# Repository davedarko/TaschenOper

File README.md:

# TaschenOper

A handheld inspired by adafruits numpad and certain pocket music devices.

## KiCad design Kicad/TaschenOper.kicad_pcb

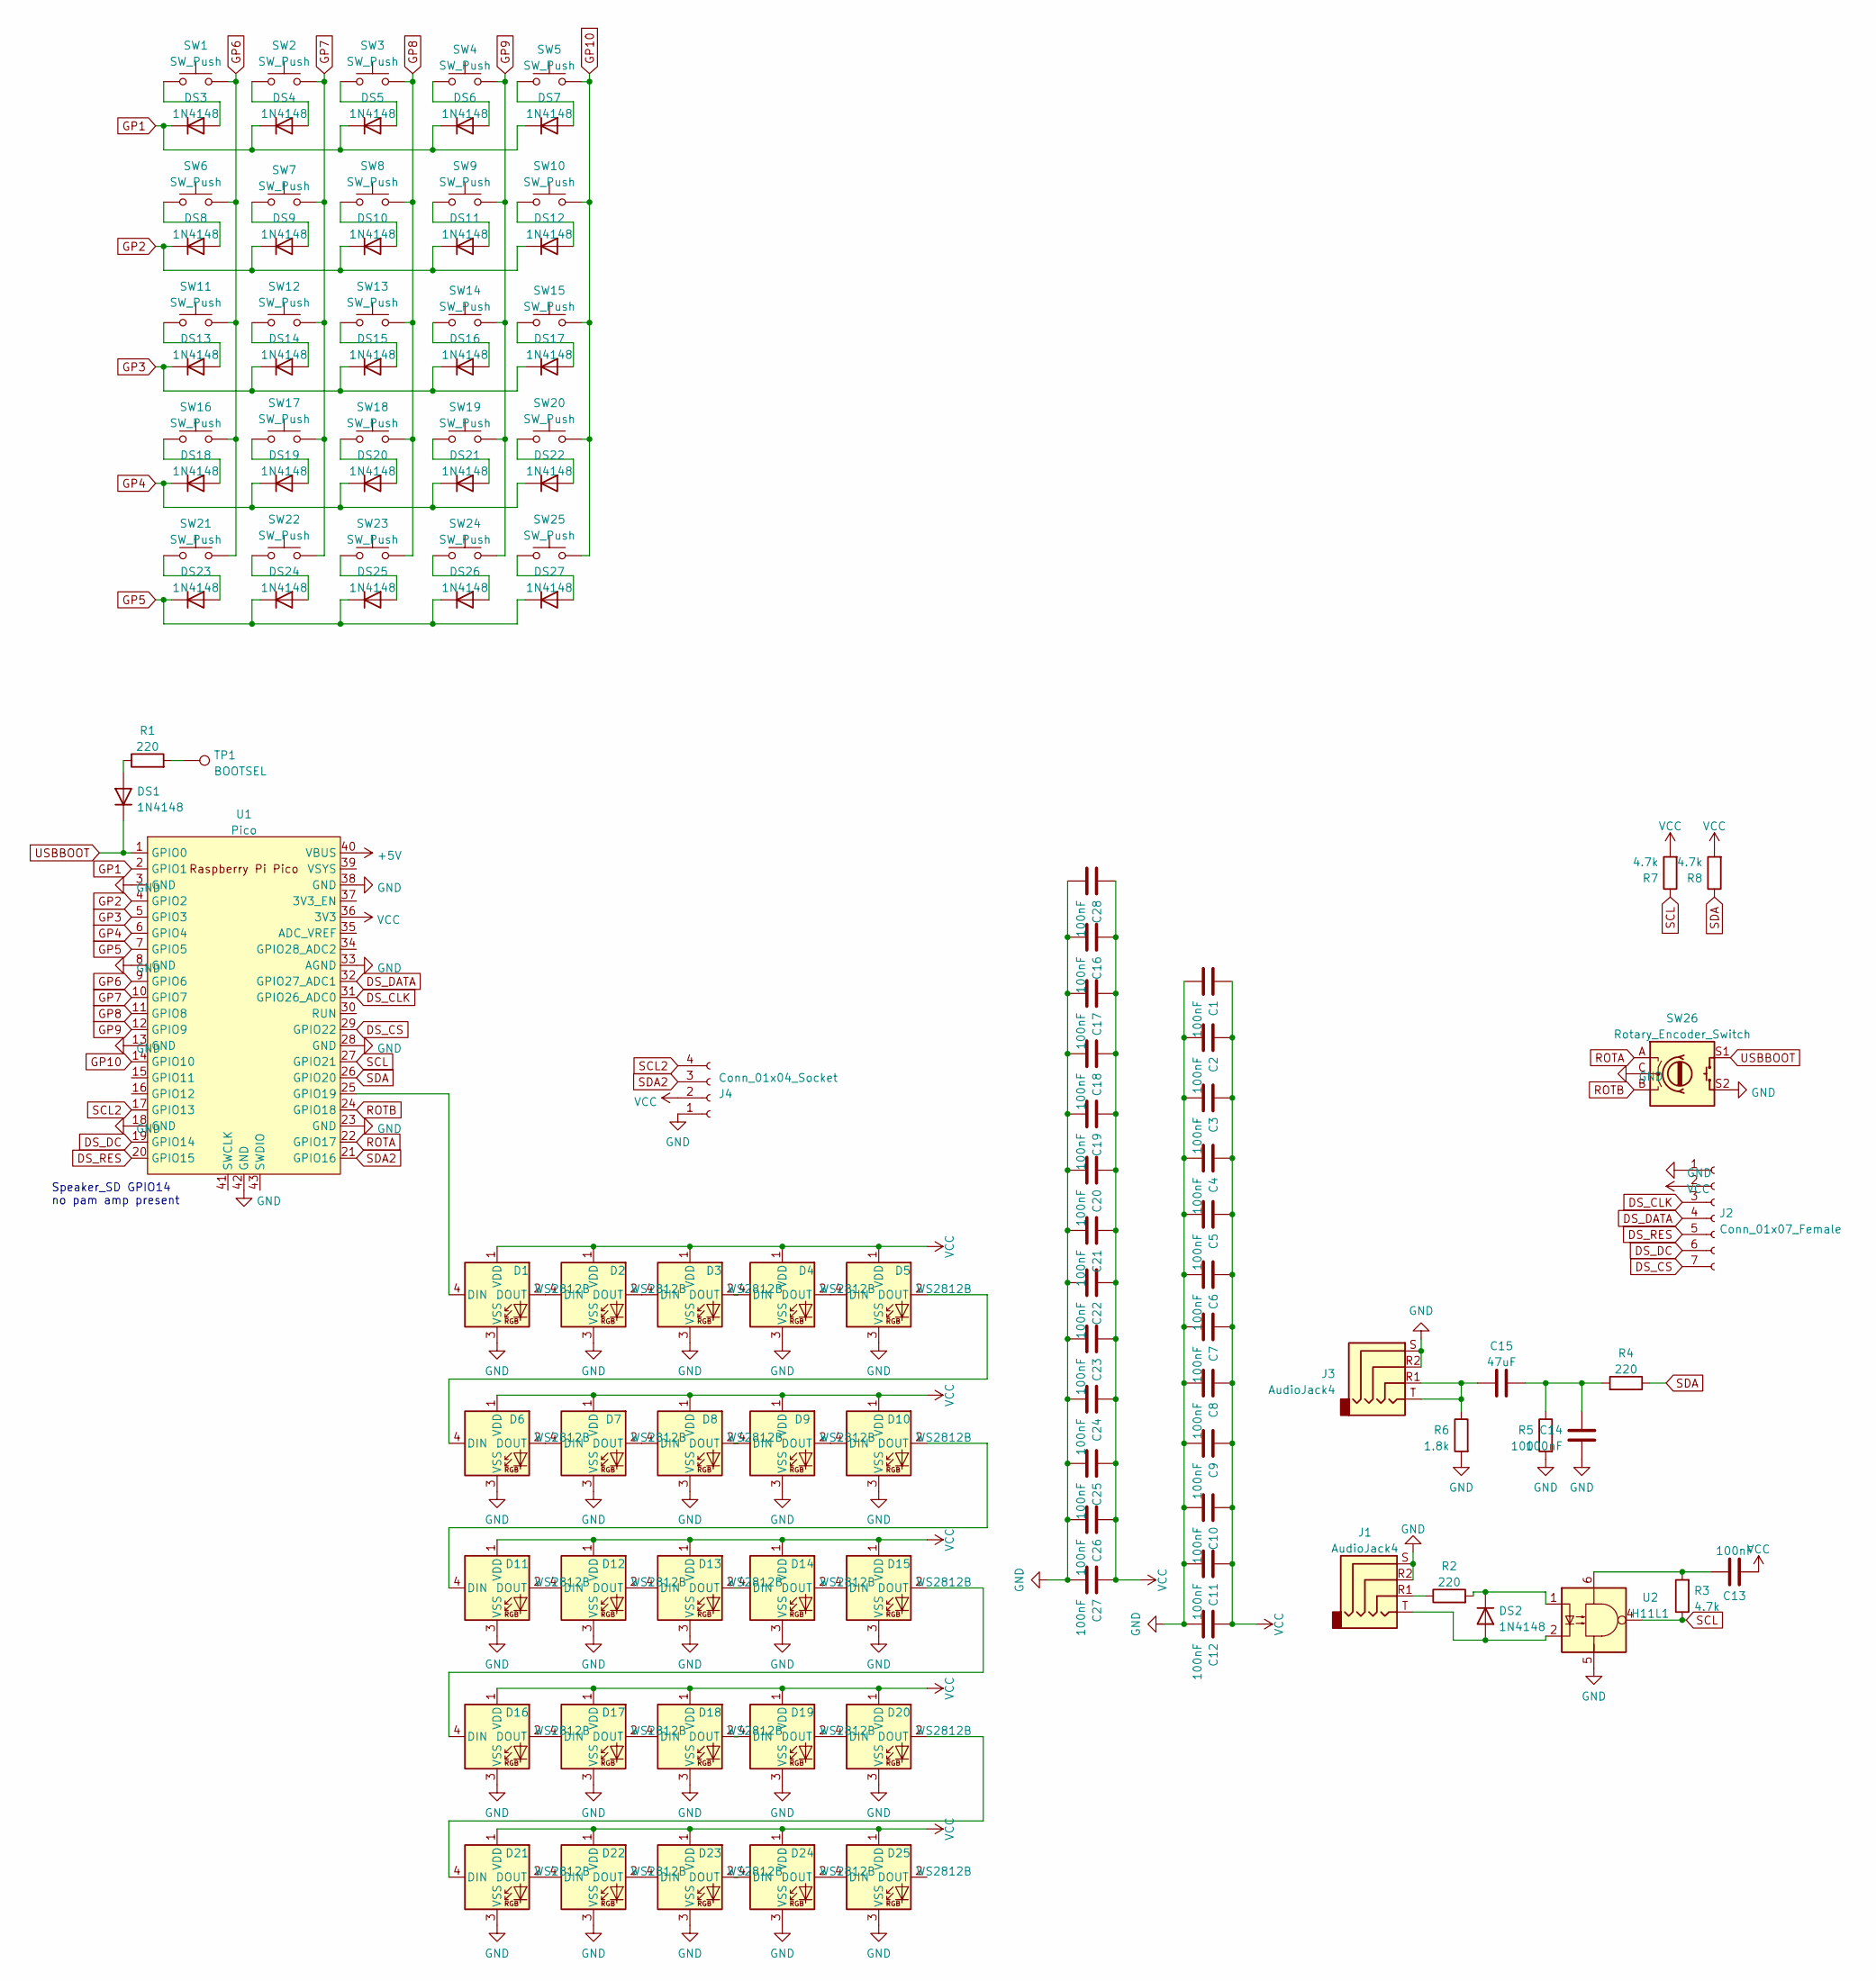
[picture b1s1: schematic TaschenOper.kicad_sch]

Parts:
C1, C2, C3, C4, C5, C6, C7, C8, C9, C10, C11, C12, C13, C14, C16, C17, C18, C19, C20, C21, C22, C23, C24, C25, C26, C27, C28: 100nF; C_0603_1608Metric_Pad1.08x0.95mm_HandSolder
C15: 47uF; C_0603_1608Metric_Pad1.08x0.95mm_HandSolder
D1, D2, D3, D4, D5, D6, D7, D8, D9, D10, D11, D12, D13, D14, D15, D16, D17, D18, D19, D20, D21, D22, D23, D24, D25: WS2812B; LED_SK6812MINI_PLCC4_3.5x3.5mm_P1.75mm
DS1, DS2, DS3, DS4, DS5, DS6, DS7, DS8, DS9, DS10, DS11, DS12, DS13, DS14, DS15, DS16, DS17, DS18, DS19, DS20, DS21, DS22, DS23, DS24, DS25, DS26, DS27: 1N4148; D_0805_2012Metric_Pad1.15x1.40mm_HandSolder
J1, J3: AudioJack4; Jack_3.5mm_PJ320D_Horizontal
J2: Conn_01x07_Female; PinHeader_1x07_P2.54mm_Vertical
J4: Conn_01x04_Socket; JST_SH_SM04B-SRSS-TB_1x04-1MP_P1.00mm_Horizontal
R1, R2, R4: 220; R_0603_1608Metric_Pad0.98x0.95mm_HandSolder
R3, R7, R8: 4.7k; R_0603_1608Metric_Pad0.98x0.95mm_HandSolder
R5: 100; R_0603_1608Metric_Pad0.98x0.95mm_HandSolder
R6: 1.8k; R_0603_1608Metric_Pad0.98x0.95mm_HandSolder
SW1, SW2, SW3, SW4, SW5, SW6, SW7, SW8, SW9, SW10, SW11, SW12, SW13, SW14, SW15, SW16, SW17, SW18, SW19, SW20, SW21, SW22, SW23, SW24, SW25: SW_Push; SW_SPST_PTS645
SW26: Rotary_Encoder_Switch; RotaryEncoder_Alps_EC11E-Switch_Vertical_H20mm_CircularMoun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
TP1: BOOTSEL; TestPoint_Pad_D1.5mm
U1: Pico; RPi_Pico_SMD
U2: H11L1; DIP-6_W8.89mm_SMDSocket_LongPads

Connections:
+5V: U1.40 (VBUS)
DS_CLK: J2.3, U1.31 (GPIO26_ADC0)
DS_CS: J2.7, U1.29 (GPIO22)
DS_DATA: J2.4, U1.32 (GPIO27_ADC1)
DS_DC: J2.6, U1.19 (GPIO14)
DS_RES: J2.5, U1.20 (GPIO15)
GND: C1.2, C2.2, C3.2, C4.2, C5.2, C6.2, C7.2, C8.2, C9.2, C10.2, C11.2, C12.2, C14.2, C16.2, C17.2, C18.2, C19.2, C20.2, C21.2, C22.2, C23.2, C24.2, C25.2, C26.2, C27.2, C28.2, D1.3 (VSS), D2.3 (VSS), D3.3 (VSS), D4.3 (VSS), D5.3 (VSS), D6.3 (VSS), D7.3 (VSS), D8.3 (VSS), D9.3 (VSS), D10.3 (VSS), D11.3 (VSS), D12.3 (VSS), D13.3 (VSS), D14.3 (VSS), D15.3 (VSS), D16.3 (VSS), D17.3 (VSS), D18.3 (VSS), D19.3 (VSS), D20.3 (VSS), D21.3 (VSS), D22.3 (VSS), D23.3 (VSS), D24.3 (VSS), D25.3 (VSS), J1.R2, J1.S, J2.1, J3.R2, J3.S, J4.1, R5.2, R6.2, SW26.C, SW26.S2, U1.3 (GND), U1.8 (GND), U1.13 (GND), U1.18 (GND), U1.23 (GND), U1.28 (GND), U1.33 (AGND), U1.38 (GND), U1.42 (GND), U2.5
GP1: DS3.1 (K), DS4.1 (K), DS5.1 (K), DS6.1 (K), DS7.1 (K), U1.2 (GPIO1)
GP2: DS8.1 (K), DS9.1 (K), DS10.1 (K), DS11.1 (K), DS12.1 (K), U1.4 (GPIO2)
GP3: DS13.1 (K), DS14.1 (K), DS15.1 (K), DS16.1 (K), DS17.1 (K), U1.5 (GPIO3)
GP4: DS18.1 (K), DS19.1 (K), DS20.1 (K), DS21.1 (K), DS22.1 (K), U1.6 (GPIO4)
GP5: DS23.1 (K), DS24.1 (K), DS25.1 (K), DS26.1 (K), DS27.1 (K), U1.7 (GPIO5)
GP6: SW1.2, SW6.2, SW11.2, SW16.2, SW21.2, U1.9 (GPIO6)
GP7: SW2.2, SW7.2, SW12.2, SW17.2, SW22.2, U1.10 (GPIO7)
GP8: SW3.2, SW8.2, SW13.2, SW18.2, SW23.2, U1.11 (GPIO8)
GP9: SW4.2, SW9.2, SW14.2, SW19.2, SW24.2, U1.12 (GPIO9)
GP10: SW5.2, SW10.2, SW15.2, SW20.2, SW25.2, U1.14 (GPIO10)
unnamed: C13.1, R3.2, U2.6
unnamed: C14.1, C15.1, R4.2, R5.1
unnamed: C15.2, J3.R1, J3.T, R6.1
unnamed: D1.4 (DIN), U1.25 (GPIO19)
unnamed: D1.2 (DOUT), D2.4 (DIN)
unnamed: D2.2 (DOUT), D3.4 (DIN)
unnamed: D3.2 (DOUT), D4.4 (DIN)
unnamed: D4.2 (DOUT), D5.4 (DIN)
unnamed: D5.2 (DOUT), D6.4 (DIN)
unnamed: D6.2 (DOUT), D7.4 (DIN)
unnamed: D7.2 (DOUT), D8.4 (DIN)
unnamed: D8.2 (DOUT), D9.4 (DIN)
unnamed: D9.2 (DOUT), D10.4 (DIN)
unnamed: D10.2 (DOUT), D11.4 (DIN)
unnamed: D11.2 (DOUT), D12.4 (DIN)
unnamed: D12.2 (DOUT), D13.4 (DIN)
unnamed: D13.2 (DOUT), D14.4 (DIN)
unnamed: D14.2 (DOUT), D15.4 (DIN)
unnamed: D15.2 (DOUT), D16.4 (DIN)
unnamed: D16.2 (DOUT), D17.4 (DIN)
unnamed: D17.2 (DOUT), D18.4 (DIN)
unnamed: D18.2 (DOUT), D19.4 (DIN)
unnamed: D19.2 (DOUT), D20.4 (DIN)
unnamed: D20.2 (DOUT), D21.4 (DIN)
unnamed: D21.2 (DOUT), D22.4 (DIN)
unnamed: D22.2 (DOUT), D23.4 (DIN)
unnamed: D23.2 (DOUT), D24.4 (DIN)
unnamed: D24.2 (DOUT), D25.4 (DIN)
unnamed: DS1.2 (A), R1.1
unnamed: DS2.2 (A), J1.T, U2.2
unnamed: DS2.1 (K), R2.2, U2.1
unnamed: DS3.2 (A), SW1.1
unnamed: DS4.2 (A), SW2.1
unnamed: DS5.2 (A), SW3.1
unnamed: DS6.2 (A), SW4.1
unnamed: DS7.2 (A), SW5.1
unnamed: DS8.2 (A), SW6.1
unnamed: DS9.2 (A), SW7.1
unnamed: DS10.2 (A), SW8.1
unnamed: DS11.2 (A), SW9.1
unnamed: DS12.2 (A), SW10.1
unnamed: DS13.2 (A), SW11.1
unnamed: DS14.2 (A), SW12.1
unnamed: DS15.2 (A), SW13.1
unnamed: DS16.2 (A), SW14.1
unnamed: DS17.2 (A), SW15.1
unnamed: DS18.2 (A), SW16.1
unnamed: DS19.2 (A), SW17.1
unnamed: DS20.2 (A), SW18.1
unnamed: DS21.2 (A), SW19.1
unnamed: DS22.2 (A), SW20.1
unnamed: DS23.2 (A), SW21.1
unnamed: DS24.2 (A), SW22.1
unnamed: DS25.2 (A), SW23.1
unnamed: DS26.2 (A), SW24.1
unnamed: DS27.2 (A), SW25.1
unnamed: J1.R1, R2.1
unnamed: R1.2, TP1.1
ROTA: SW26.A, U1.22 (GPIO17)
ROTB: SW26.B, U1.24 (GPIO18)
SCL: R3.1, R7.1, U1.27 (GPIO21), U2.4
SCL2: J4.4, U1.17 (GPIO13)
SDA: R4.1, R8.1, U1.26 (GPIO20)
SDA2: J4.3, U1.21 (GPIO16)
USBBOOT: DS1.1 (K), SW26.S1, U1.1 (GPIO0)
VCC: C1.1, C2.1, C3.1, C4.1, C5.1, C6.1, C7.1, C8.1, C9.1, C10.1, C11.1, C12.1, C13.2, C16.1, C17.1, C18.1, C19.1, C20.1, C21.1, C22.1, C23.1, C24.1, C25.1, C26.1, C27.1, C28.1, D1.1 (VDD), D2.1 (VDD), D3.1 (VDD), D4.1 (VDD), D5.1 (VDD), D6.1 (VDD), D7.1 (VDD), D8.1 (VDD), D9.1 (VDD), D10.1 (VDD), D11.1 (VDD), D12.1 (VDD), D13.1 (VDD), D14.1 (VDD), D15.1 (VDD), D16.1 (VDD), D17.1 (VDD), D18.1 (VDD), D19.1 (VDD), D20.1 (VDD), D21.1 (VDD), D22.1 (VDD), D23.1 (VDD), D24.1 (VDD), D25.1 (VDD), J2.2, J4.2, R7.2, R8.2, U1.36 (3V3)

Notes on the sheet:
Speaker_SD GPIO14 no pam amp present

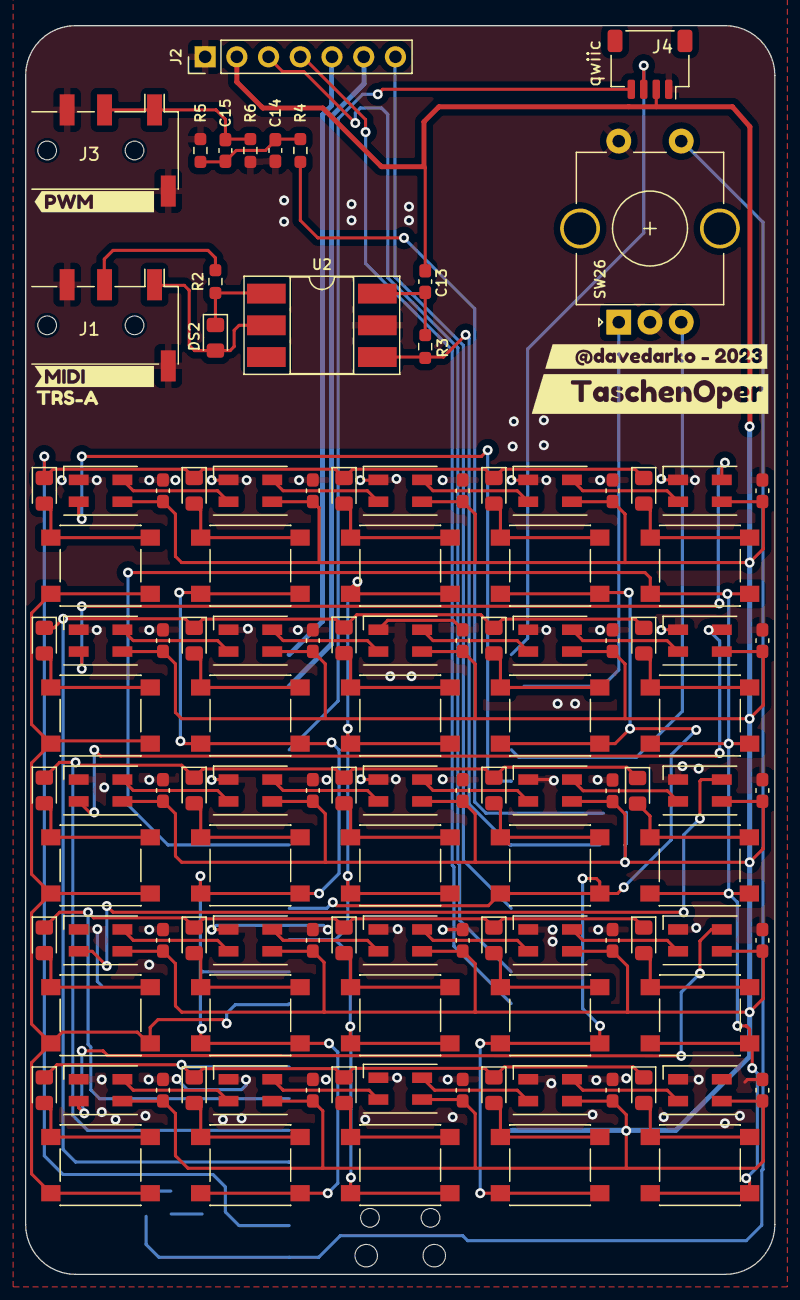
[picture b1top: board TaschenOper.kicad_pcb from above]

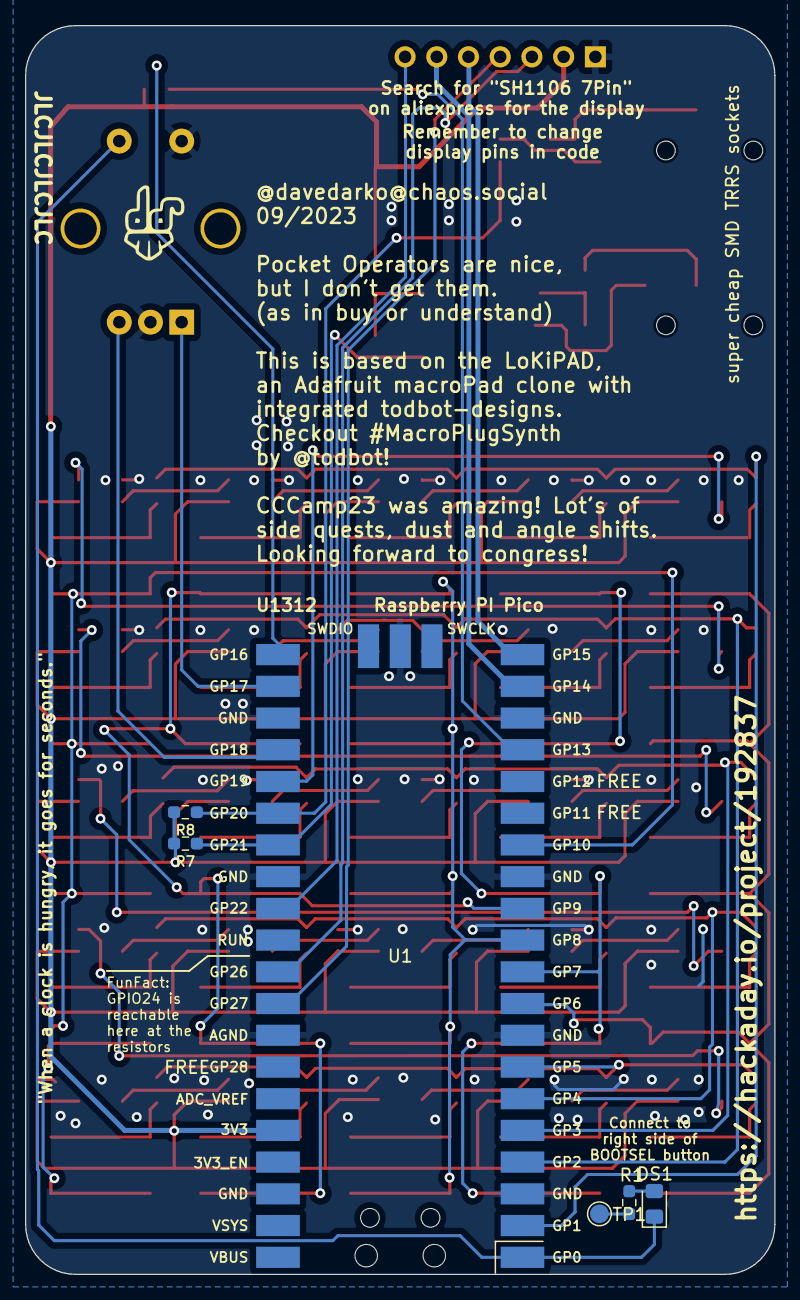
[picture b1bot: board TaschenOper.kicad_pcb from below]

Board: 2 copper layers, 60.0 x 100.0 mm, 127 parts (7 on the bottom side), 82 nets.

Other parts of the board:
Ref**: Val**; davedarko_logo_silk_outline
kibuzzard-63D676B5: G***; kibuzzard-63D676B5
kibuzzard-63D67702: G***; kibuzzard-63D67702
kibuzzard-63D67711: G***; kibuzzard-63D67711
kibuzzard-63E7EF8E: G***; kibuzzard-63E7EF8E
kibuzzard-6504AD62: G***; kibuzzard-6504AD62

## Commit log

2024-09-01 upload all
